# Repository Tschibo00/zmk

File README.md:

# zmk

## WARNING
This project is a personal project, i just built one prototype. It's not considered complete, nor tested or error-free.

I won't develop this much, just releasing it as-is for anybody knowledgable picking up and maybe building upon it.

It is NOT ready to take the files and produce a working keyboard!

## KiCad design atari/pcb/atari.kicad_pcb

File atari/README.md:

# AtaKi
Wireless universal 40% keyboard in a 12x4U format, including mounting holes for BM40 cases and gaskets.
Will be using ZMK on a nice!nano

The PCB supports multiple configurations, including Katana with 0.5U indent and QAZ, also multiple bottow row configs are possible.
(almost) all switches are mounted sideways to have better stability with the overlapping footprints. Also it's no clearance problem with tested switches/caps and it supports the modified Selectric keycaps (see https://github.com/Tschibo00/qmk/tree/main/hacktrick for details on the idea)

## WARNING
This project is a personal project, i just built one prototype. It's not considered complete, nor tested or error-free.

I won't develop this much, just releasing it as-is for anybody knowledgable picking up and maybe building upon it.

It is NOT ready to take the files and produce a working keyboard!

## How to build
To not struggle when soldering, it should be done in the following order:
- solder all diodes (and resistor if equipped) first
- solder the two switches on opposite of MCU
  - if you want to put the MCU as low as possible, cut the pins of the switches first to sit quite flush with the PCB
- solder the MCU
  - put the short ends of the headers through the PCB, long end goes through the MCU
  - if you want to put the MCU flush down, solder headers to PCB first, then remove the spacers on the headers. Put MCU on and solder, clip headers
- solder remaining switches
  - triple-check with every row that your soldering the correct layout. put the required caps on the switches to see, which holes you need to solder to

# Todos
- [x] add PCB artwork
- [x] order the thing
- [x] hack firmware
- [ ] design Atari 130XE style case including function keys
- [ ] boast about it on r/mk
- [x] fix PCB (esp. encoder mount pads)
- [x] add note to U1 to put nano on bottom side
- [x] add traces to daughter board
- [x] add missing Atari footprints
- [x] move name+link to central bottom row, enlarge a bit
- [x] move reset switch because it's blocking the usb
- [x] add joystick ports
- [x] create base keymap
- [x] create additional keymaps, e.g. Katana
- [x] add LED connector

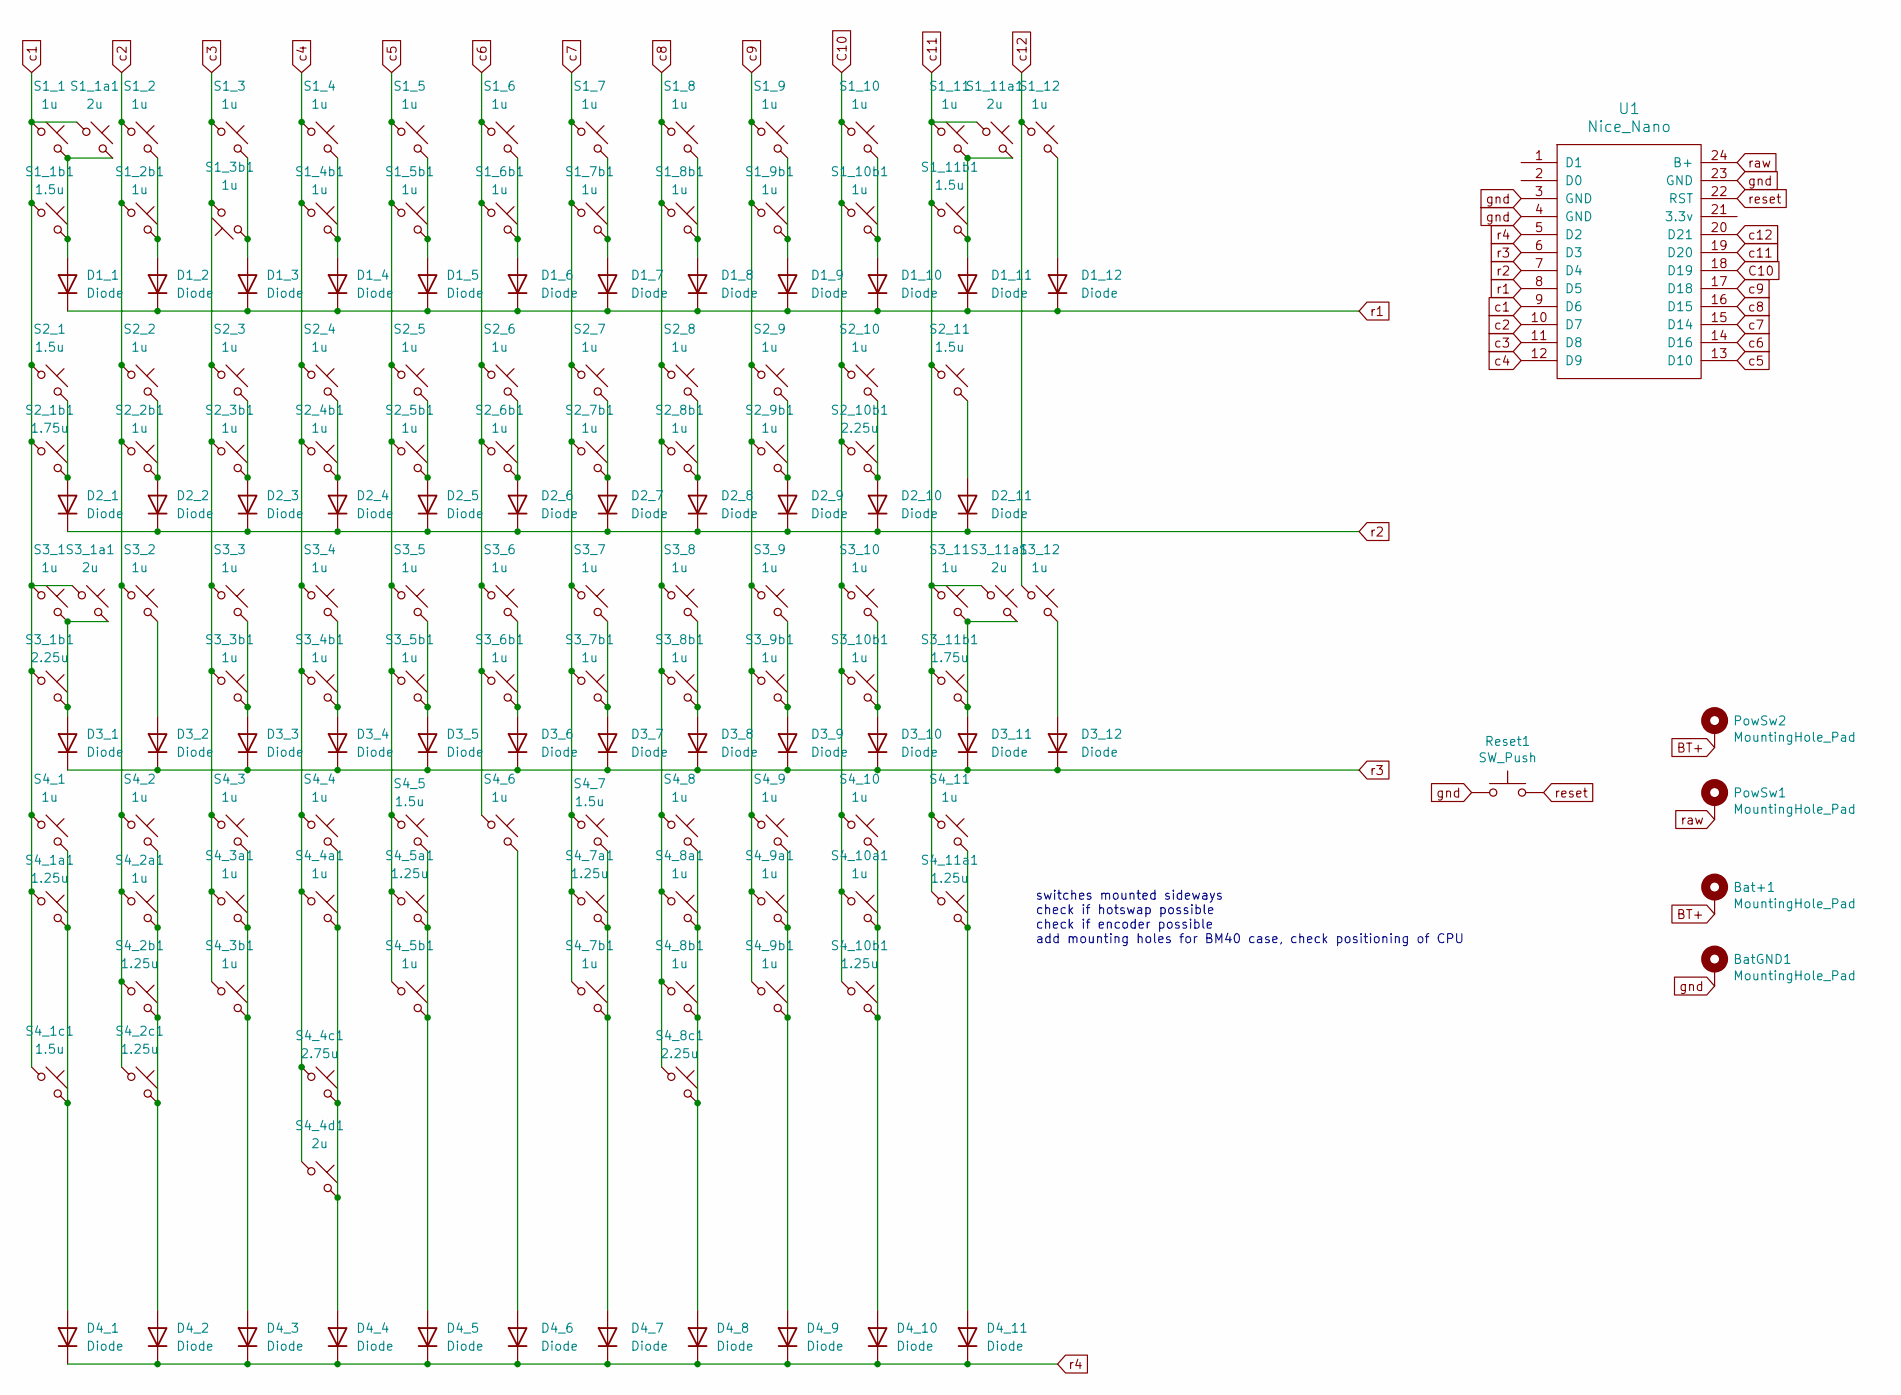
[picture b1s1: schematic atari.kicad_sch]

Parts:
Bat+1: MountingHole_Pad; SolderWire-0.5sqmm_1x01_D0.9mm_OD2.1mm
BatGND1: MountingHole_Pad; SolderWire-0.5sqmm_1x01_D0.9mm_OD2.1mm
D1_1, D1_2, D1_3, D1_4, D1_5, D1_6, D1_7, D1_8, D1_9, D1_10, D1_11, D1_12, D2_1, D2_2, D2_3, D2_4, D2_5, D2_6, D2_7, D2_8, D2_9, D2_10, D2_11, D3_1, D3_2, D3_3, D3_4, D3_5, D3_6, D3_7, D3_8, D3_9, D3_10, D3_11, D3_12, D4_1, D4_2, D4_3, D4_4, D4_5, D4_6, D4_7, D4_8, D4_9, D4_10, D4_11: Diode; Diode_DO-35
PowSw1, PowSw2: MountingHole_Pad; SolderWire-0.5sqmm_1x01_D0.9mm_OD2.1mm
Reset1: SW_Push; SW_PUSH_6mm_H4.3mm
S1_1, S1_2, S1_2b1, S1_3, S1_3b1, S1_4, S1_4b1, S1_5, S1_5b1, S1_6, S1_6b1, S1_7, S1_7b1, S1_8, S1_8b1, S1_9, S1_9b1, S1_10, S1_10b1, S1_11, S1_12, S2_2, S2_2b1, S2_3, S2_3b1, S2_4, S2_4b1, S2_5, S2_5b1, S2_6, S2_6b1, S2_7, S2_7b1, S2_8, S2_8b1, S2_9, S2_9b1, S2_10, S3_1, S3_2, S3_3, S3_3b1, S3_4, S3_4b1, S3_5, S3_5b1, S3_6, S3_6b1, S3_7, S3_7b1, S3_8, S3_8b1, S3_9, S3_9b1, S3_10, S3_10b1, S3_11, S3_12, S4_1, S4_2, S4_2a1, S4_3, S4_3a1, S4_3b1, S4_4, S4_4a1, S4_5b1, S4_6, S4_7b1, S4_8, S4_8a1, S4_8b1, S4_9, S4_9a1, S4_9b1, S4_10, S4_10a1, S4_11: 1u; MX_PCB_1.00u
S1_1a1, S1_11a1, S3_1a1, S3_11a1, S4_4d1: 2u; MX_PCB_2.00u_90deg
S1_1b1, S1_11b1, S2_1, S2_11, S4_1c1, S4_5, S4_7: 1.5u; MX_PCB_1.50u_90deg
S2_1b1, S3_11b1: 1.75u; MX_PCB_1.75u_90deg
S2_10b1, S3_1b1, S4_8c1: 2.25u; MX_PCB_2.25u_90deg
S4_1a1, S4_2b1, S4_2c1, S4_5a1, S4_7a1, S4_10b1, S4_11a1: 1.25u; MX_PCB_1.25u_90deg
S4_4c1: 2.75u; MX_PCB_2.75u_90deg
U1: Nice_Nano; Nice_Nano_V2

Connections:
BT+: Bat+1.1, PowSw2.1; also elsewhere on the board
C10: S1_10.1, S1_10b1.1, S2_10.1, S2_10b1.1, S3_10.1, S3_10b1.1, S4_10.1, S4_10a1.1, S4_10b1.1, U1.18 (D19)
unnamed: D1_1.2 (A), S1_1.2, S1_1a1.2, S1_1b1.2
unnamed: D1_2.2 (A), S1_2.2, S1_2b1.2
unnamed: D1_3.2 (A), S1_3.2, S1_3b1.1
unnamed: D1_4.2 (A), S1_4.2, S1_4b1.2
unnamed: D1_5.2 (A), S1_5.2, S1_5b1.2
unnamed: D1_6.2 (A), S1_6.2, S1_6b1.2
unnamed: D1_7.2 (A), S1_7.2, S1_7b1.2
unnamed: D1_8.2 (A), S1_8.2, S1_8b1.2
unnamed: D1_9.2 (A), S1_9.2, S1_9b1.2
unnamed: D1_10.2 (A), S1_10.2, S1_10b1.2
unnamed: D1_11.2 (A), S1_11.2, S1_11a1.2, S1_11b1.2
unnamed: D1_12.2 (A), S1_12.2
unnamed: D2_1.2 (A), S2_1.2, S2_1b1.2
unnamed: D2_2.2 (A), S2_2.2, S2_2b1.2
unnamed: D2_3.2 (A), S2_3.2, S2_3b1.2
unnamed: D2_4.2 (A), S2_4.2, S2_4b1.2
unnamed: D2_5.2 (A), S2_5.2, S2_5b1.2
unnamed: D2_6.2 (A), S2_6.2, S2_6b1.2
unnamed: D2_7.2 (A), S2_7.2, S2_7b1.2
unnamed: D2_8.2 (A), S2_8.2, S2_8b1.2
unnamed: D2_9.2 (A), S2_9.2, S2_9b1.2
unnamed: D2_10.2 (A), S2_10.2, S2_10b1.2
unnamed: D2_11.2 (A), S2_11.2
unnamed: D3_1.2 (A), S3_1.2, S3_1a1.2, S3_1b1.2
unnamed: D3_2.2 (A), S3_2.2
unnamed: D3_3.2 (A), S3_3.2, S3_3b1.2
unnamed: D3_4.2 (A), S3_4.2, S3_4b1.2
unnamed: D3_5.2 (A), S3_5.2, S3_5b1.2
unnamed: D3_6.2 (A), S3_6.2, S3_6b1.2
unnamed: D3_7.2 (A), S3_7.2, S3_7b1.2
unnamed: D3_8.2 (A), S3_8.2, S3_8b1.2
unnamed: D3_9.2 (A), S3_9.2, S3_9b1.2
unnamed: D3_10.2 (A), S3_10.2, S3_10b1.2
unnamed: D3_11.2 (A), S3_11.2, S3_11a1.2, S3_11b1.2
unnamed: D3_12.2 (A), S3_12.2
unnamed: D4_1.2 (A), S4_1.2, S4_1a1.2, S4_1c1.2
unnamed: D4_2.2 (A), S4_2.2, S4_2a1.2, S4_2b1.2, S4_2c1.2
unnamed: D4_3.2 (A), S4_3.2, S4_3a1.2, S4_3b1.2
unnamed: D4_4.2 (A), S4_4.2, S4_4a1.2, S4_4c1.2, S4_4d1.2
unnamed: D4_5.2 (A), S4_5.2, S4_5a1.2, S4_5b1.2
unnamed: D4_6.2 (A), S4_6.2
unnamed: D4_7.2 (A), S4_7.2, S4_7a1.2, S4_7b1.2
unnamed: D4_8.2 (A), S4_8.2, S4_8a1.2, S4_8b1.2, S4_8c1.2
unnamed: D4_9.2 (A), S4_9.2, S4_9a1.2, S4_9b1.2
unnamed: D4_10.2 (A), S4_10.2, S4_10a1.2, S4_10b1.2
unnamed: D4_11.2 (A), S4_11.2, S4_11a1.2
c1: S1_1.1, S1_1a1.1, S1_1b1.1, S2_1.1, S2_1b1.1, S3_1.1, S3_1a1.1, S3_1b1.1, S4_1.1, S4_1a1.1, S4_1c1.1, U1.9 (D6)
c2: S1_2.1, S1_2b1.1, S2_2.1, S2_2b1.1, S3_2.1, S4_2.1, S4_2a1.1, S4_2b1.1, S4_2c1.1, U1.10 (D7)
c3: S1_3.1, S1_3b1.2, S2_3.1, S2_3b1.1, S3_3.1, S3_3b1.1, S4_3.1, S4_3a1.1, S4_3b1.1, U1.11 (D8)
c4: S1_4.1, S1_4b1.1, S2_4.1, S2_4b1.1, S3_4.1, S3_4b1.1, S4_4.1, S4_4a1.1, S4_4c1.1, S4_4d1.1, U1.12 (D9)
c5: S1_5.1, S1_5b1.1, S2_5.1, S2_5b1.1, S3_5.1, S3_5b1.1, S4_5.1, S4_5a1.1, S4_5b1.1, U1.13 (D10)
c6: S1_6.1, S1_6b1.1, S2_6.1, S2_6b1.1, S3_6.1, S3_6b1.1, S4_6.1, U1.14 (D16)
c7: S1_7.1, S1_7b1.1, S2_7.1, S2_7b1.1, S3_7.1, S3_7b1.1, S4_7.1, S4_7a1.1, S4_7b1.1, U1.15 (D14)
c8: S1_8.1, S1_8b1.1, S2_8.1, S2_8b1.1, S3_8.1, S3_8b1.1, S4_8.1, S4_8a1.1, S4_8b1.1, S4_8c1.1, U1.16 (D15)
c9: S1_9.1, S1_9b1.1, S2_9.1, S2_9b1.1, S3_9.1, S3_9b1.1, S4_9.1, S4_9a1.1, S4_9b1.1, U1.17 (D18)
c11: S1_11.1, S1_11a1.1, S1_11b1.1, S2_11.1, S3_11.1, S3_11a1.1, S3_11b1.1, S4_11.1, S4_11a1.1, U1.19 (D20)
c12: S1_12.1, S3_12.1, U1.20 (D21)
gnd: BatGND1.1, Reset1.1, U1.3 (GND), U1.4 (GND), U1.23 (GND); also elsewhere on the board
r1: D1_1.1 (K), D1_2.1 (K), D1_3.1 (K), D1_4.1 (K), D1_5.1 (K), D1_6.1 (K), D1_7.1 (K), D1_8.1 (K), D1_9.1 (K), D1_10.1 (K), D1_11.1 (K), D1_12.1 (K), U1.8 (D5)
r2: D2_1.1 (K), D2_2.1 (K), D2_3.1 (K), D2_4.1 (K), D2_5.1 (K), D2_6.1 (K), D2_7.1 (K), D2_8.1 (K), D2_9.1 (K), D2_10.1 (K), D2_11.1 (K), U1.7 (D4)
r3: D3_1.1 (K), D3_2.1 (K), D3_3.1 (K), D3_4.1 (K), D3_5.1 (K), D3_6.1 (K), D3_7.1 (K), D3_8.1 (K), D3_9.1 (K), D3_10.1 (K), D3_11.1 (K), D3_12.1 (K), U1.6 (D3)
r4: D4_1.1 (K), D4_2.1 (K), D4_3.1 (K), D4_4.1 (K), D4_5.1 (K), D4_6.1 (K), D4_7.1 (K), D4_8.1 (K), D4_9.1 (K), D4_10.1 (K), D4_11.1 (K), U1.5 (D2)
raw: PowSw1.1, U1.24 (B+)
reset: Reset1.2, U1.22 (RST)

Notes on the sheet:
switches mounted sideways check if hotswap possible check if encoder possible add mounting holes for BM40 case, check positioning of CPU

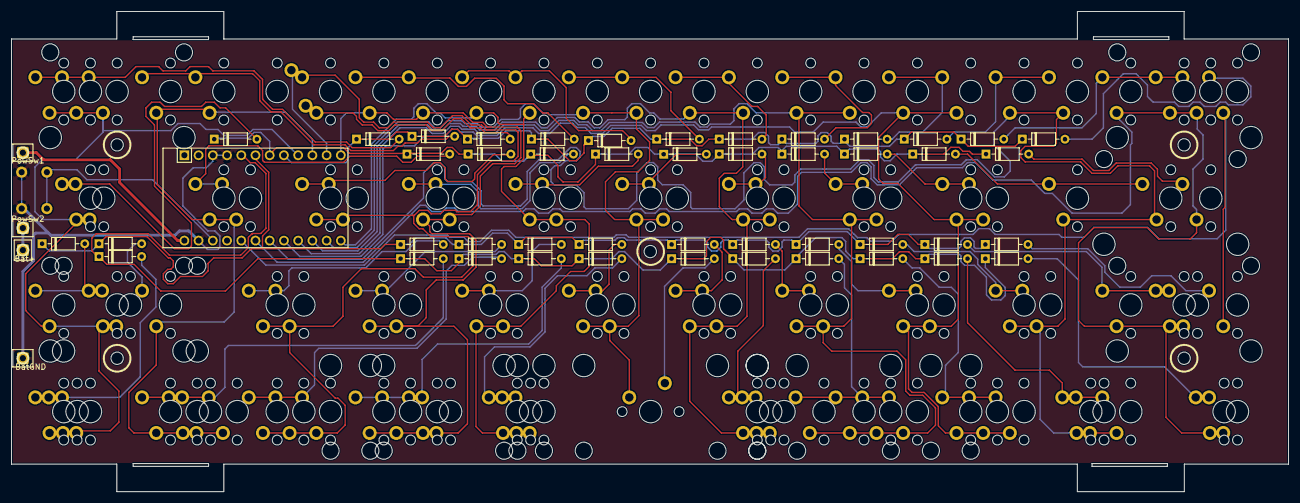
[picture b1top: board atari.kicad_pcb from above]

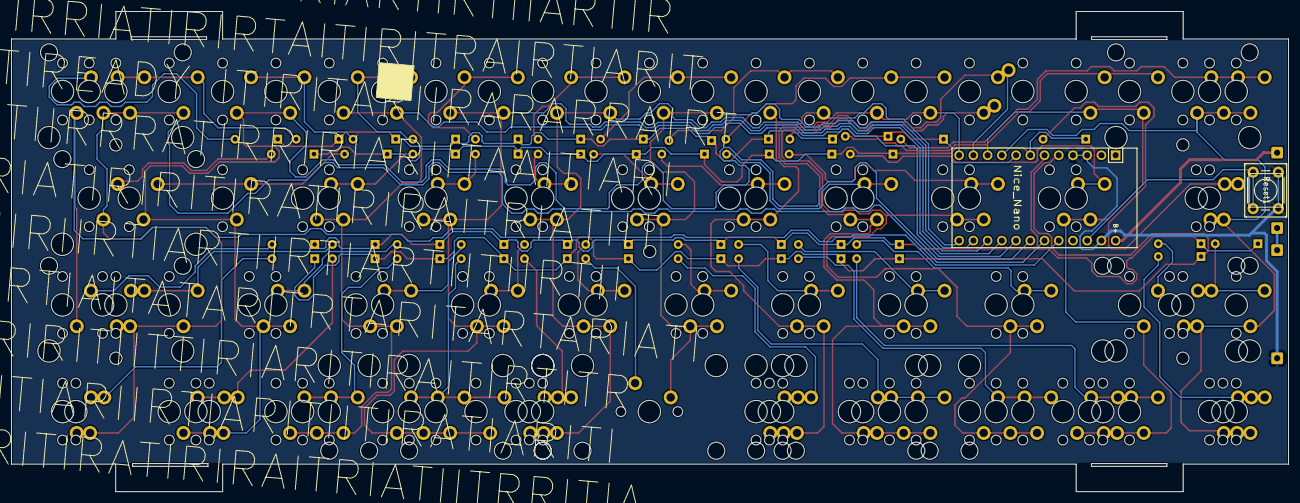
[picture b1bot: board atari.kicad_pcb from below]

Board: 2 copper layers, 228.0 x 85.7 mm, 155 parts (2 on the bottom side), 66 nets.

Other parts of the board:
Bat+: MountingHole_Pad; SolderWire-0.5sqmm_1x01_D0.9mm_OD2.1mm
BatGND: MountingHole_Pad; SolderWire-0.5sqmm_1x01_D0.9mm_OD2.1mm

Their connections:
BT+: Bat+.1; also elsewhere on the board
gnd: BatGND.1; also elsewhere on the board

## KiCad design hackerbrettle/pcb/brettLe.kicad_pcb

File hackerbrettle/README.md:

# HackerBrettLe
Wireless split version of my usual keyboard layout, (more or less) migrated to ZMK.

34-key, gasket mount, mag-lock capable, using nice!nano

## WARNING
This project is a personal project, i just built one prototype. It's not considered complete, nor tested or error-free.

I won't develop this much, just releasing it as-is for anybody knowledgable picking up and maybe building upon it.

It is NOT ready to take the files and produce a working keyboard!

# Todos
- [x] fix shifted symbol layer keys
- [x] fix right GUI
- [x] check delay on longer strings (esp. execute-macros)
- [x] check HRM functionality
- [x] check mod-behaviour on thumb keys

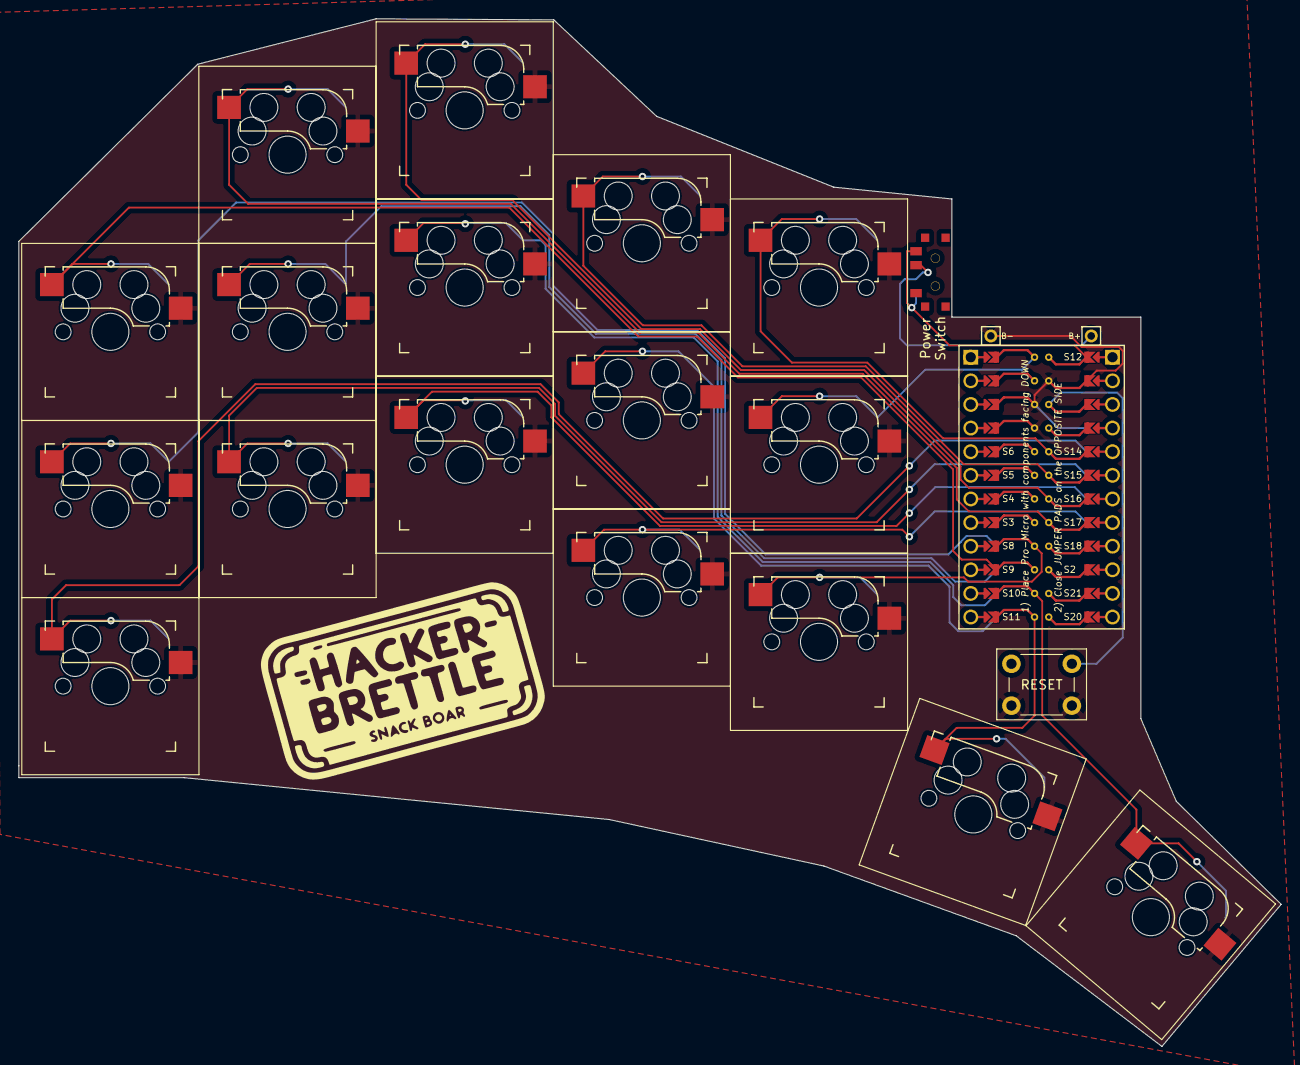
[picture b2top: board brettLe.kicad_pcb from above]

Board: 2 copper layers, 135.7 x 110.5 mm, 23 parts (1 on the bottom side), 21 nets.

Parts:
Bat+r1: MountingHole_Pad; 1pin_conn
BatGND1: MountingHole_Pad; 1pin_conn
RST_B: SW_Push; SW_PUSH_6mm_H4.3mm
SW2, SW3, SW4, SW5, SW6, SW8, SW9, SW10, SW11, SW12, SW14, SW15, SW16, SW17, SW18, SW20, SW21: SW_Push; Kailh_socket_MX_reversible_sameside
SW_POWERR1: SW_SPDT; SPDT_C128955
SW_POWERR_BK: SW_SPDT; SPDT_C128955r
U1: ProMicro-kbd; ProMicro_facedown

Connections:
BT+_r: Bat+r1.1, SW_POWERR1.2 (B), SW_POWERR_BK.2
Switch1: SW2.1, U1.10
Switch2: SW3.1, U1.17
Switch3: SW4.1, U1.18
Switch4: SW5.1, U1.19
Switch5: SW6.1, U1.20
Switch6: SW8.1, U1.16
Switch7: SW9.1, U1.15
Switch8: SW10.1, U1.14
Switch9: SW11.1, U1.13
Switch10: SW12.1, U1.1
Switch11: SW14.1, U1.5
Switch12: SW15.1, U1.6
Switch13: SW16.1, U1.7
Switch14: SW17.1, U1.8
Switch15: SW18.1, U1.9
Switch16: SW21.1, U1.11
Switch17: SW20.1, U1.12
gnd: BatGND1.1, RST_B.1, SW2.2, SW3.2, SW4.2, SW5.2, SW6.2, SW8.2, SW9.2, SW10.2, SW11.2, SW12.2, SW14.2, SW15.2, SW16.2, SW17.2, SW18.2, SW20.2, SW21.2, U1.3, U1.4, U1.23
raw: SW_POWERR1.3 (C), SW_POWERR_BK.3, U1.24
reset: RST_B.2, U1.22

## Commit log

2024-11-16 Initial User Config.
2024-11-17 colemak;first macro for testing
2024-11-17 corrected build.yaml
2024-11-17 switched from my name to template to satisfy shitty build process
2024-11-17 corrected syntax
2024-11-17 urgs
2025-11-25 modified from urob's implementation to support overlapping 1- and 2-key sequences
2025-11-25 example overlapping leader key config
2025-11-25 change to index positions for sequence definition
2025-12-16 moved diodes in; cleanup; fixed fill
2025-12-17 cleanup; fill remaining holes where possible
2025-12-18 more cleanup; optimizing fill ratio
2025-12-24 added function key breakoff
2025-12-26 added optional encoder
2025-12-28 cleanup
2025-12-28 added pacman decoration
2025-12-30 adding deco;cleanup;optimizations
2026-01-23 initial keymap (not working yet)
2026-01-25 added option for additional layouts; small fixes
2026-01-27 initial version of updated design
    - added joystick port
    - made switch alignment consistent
    - fixed missing traces
    - moved reset button away from USB port
    - added LED connector
    - removed option buttons daughterboard (see v1 for that)
2026-01-27 moved to v1 subfolder
2026-01-27 fixed issues, added production file
2026-01-27 added build instructions
